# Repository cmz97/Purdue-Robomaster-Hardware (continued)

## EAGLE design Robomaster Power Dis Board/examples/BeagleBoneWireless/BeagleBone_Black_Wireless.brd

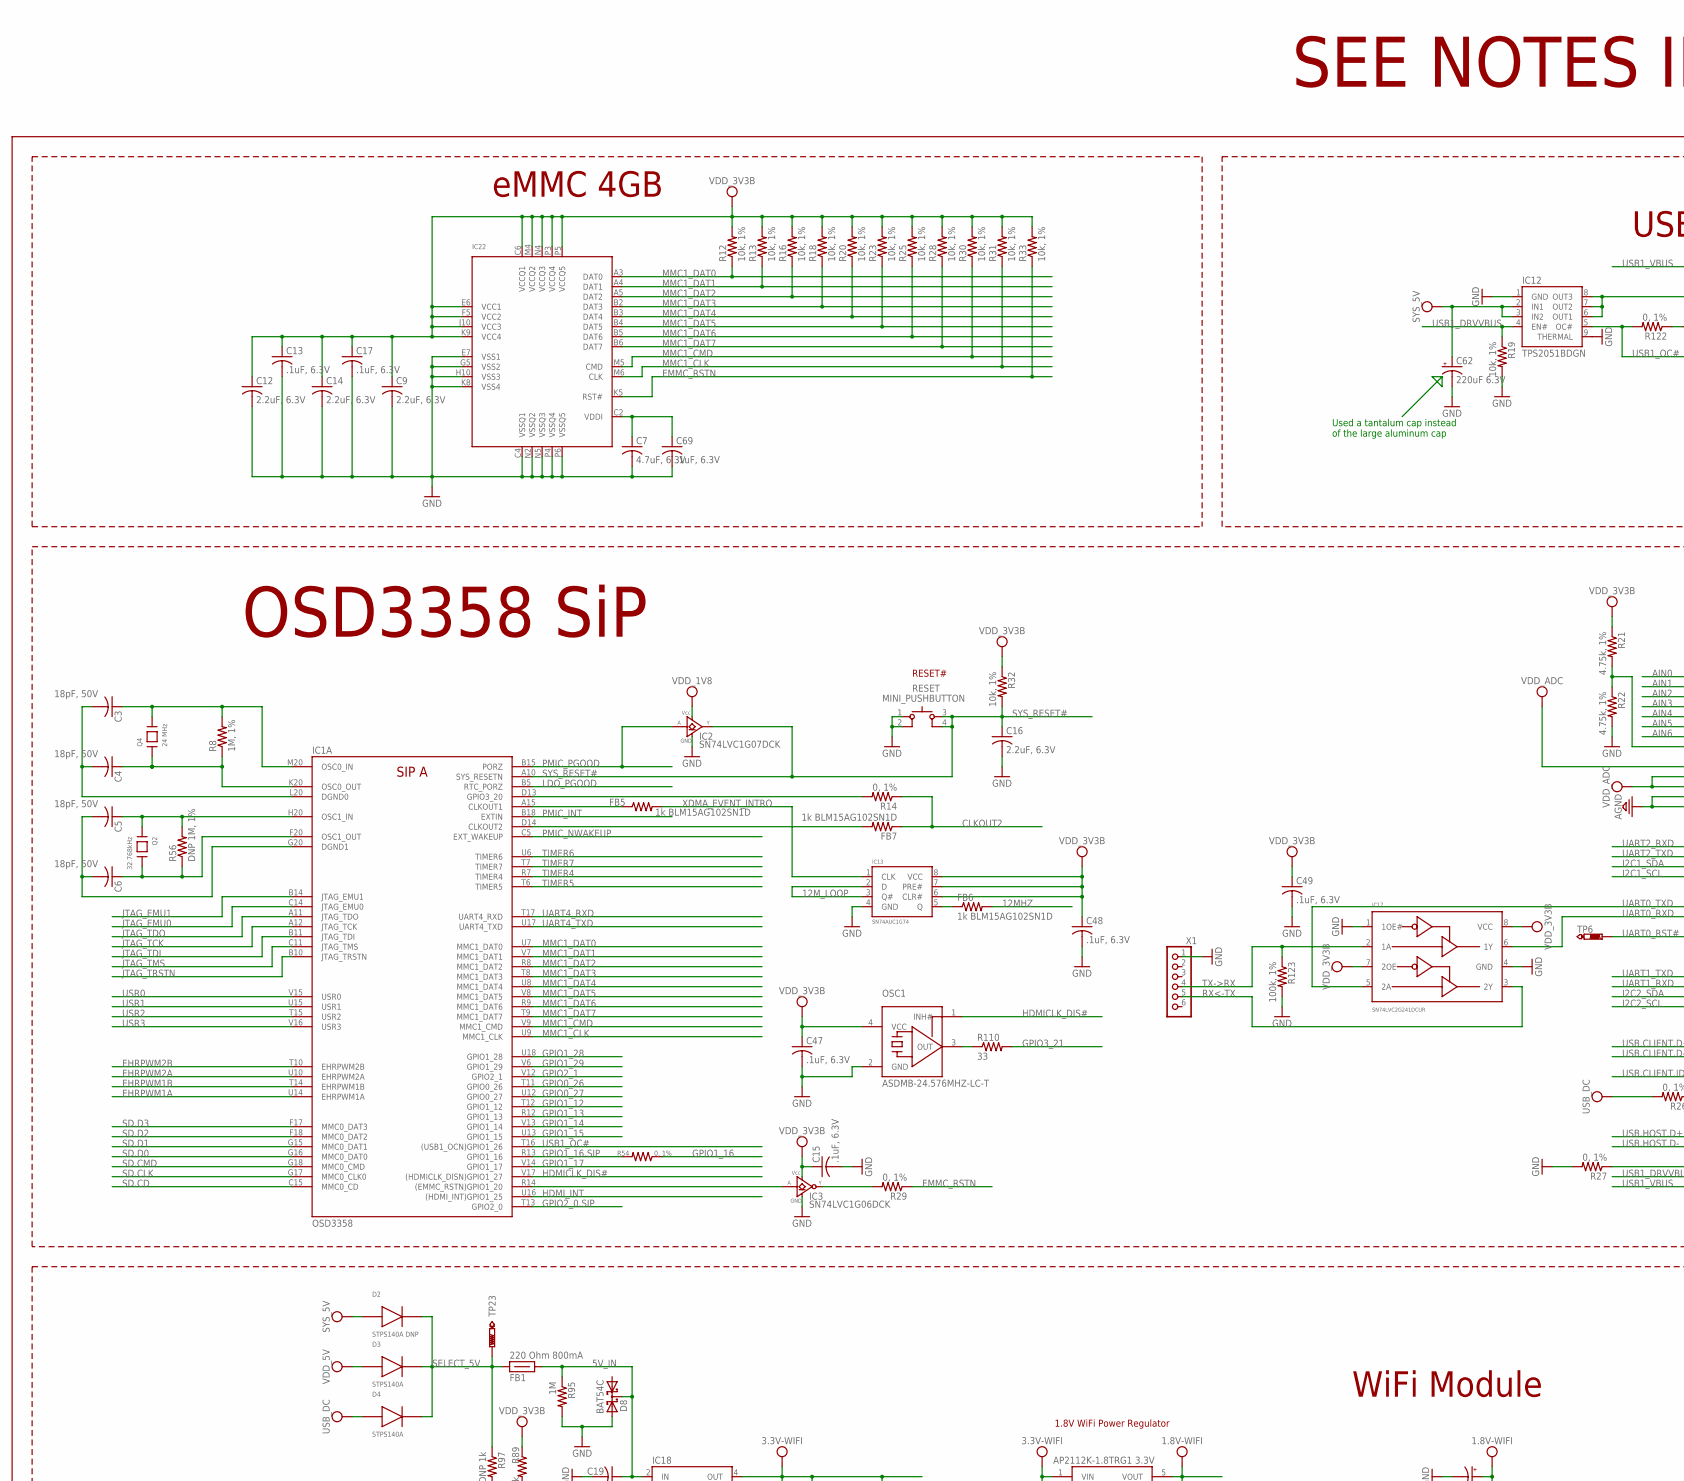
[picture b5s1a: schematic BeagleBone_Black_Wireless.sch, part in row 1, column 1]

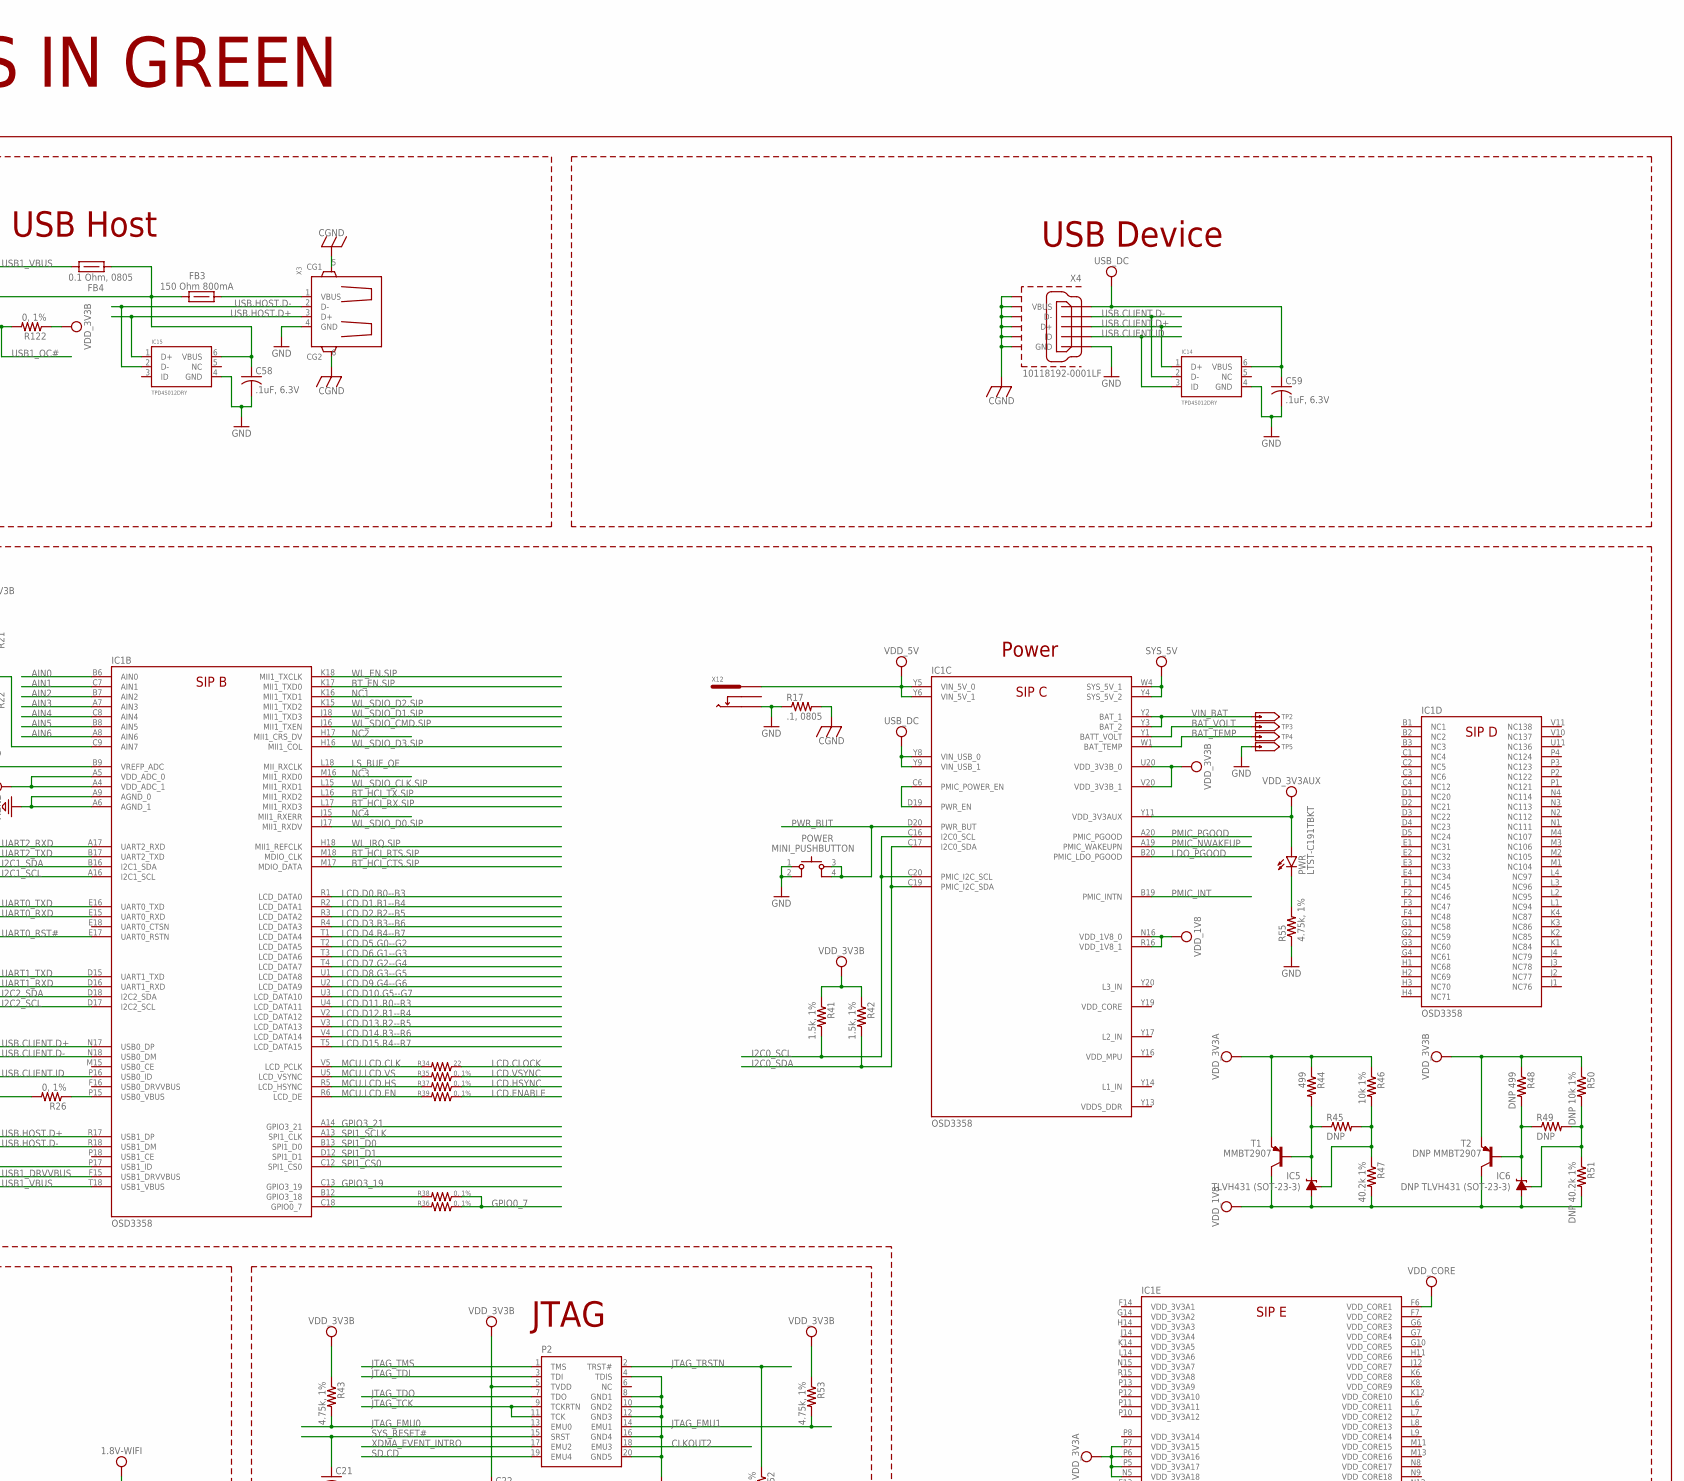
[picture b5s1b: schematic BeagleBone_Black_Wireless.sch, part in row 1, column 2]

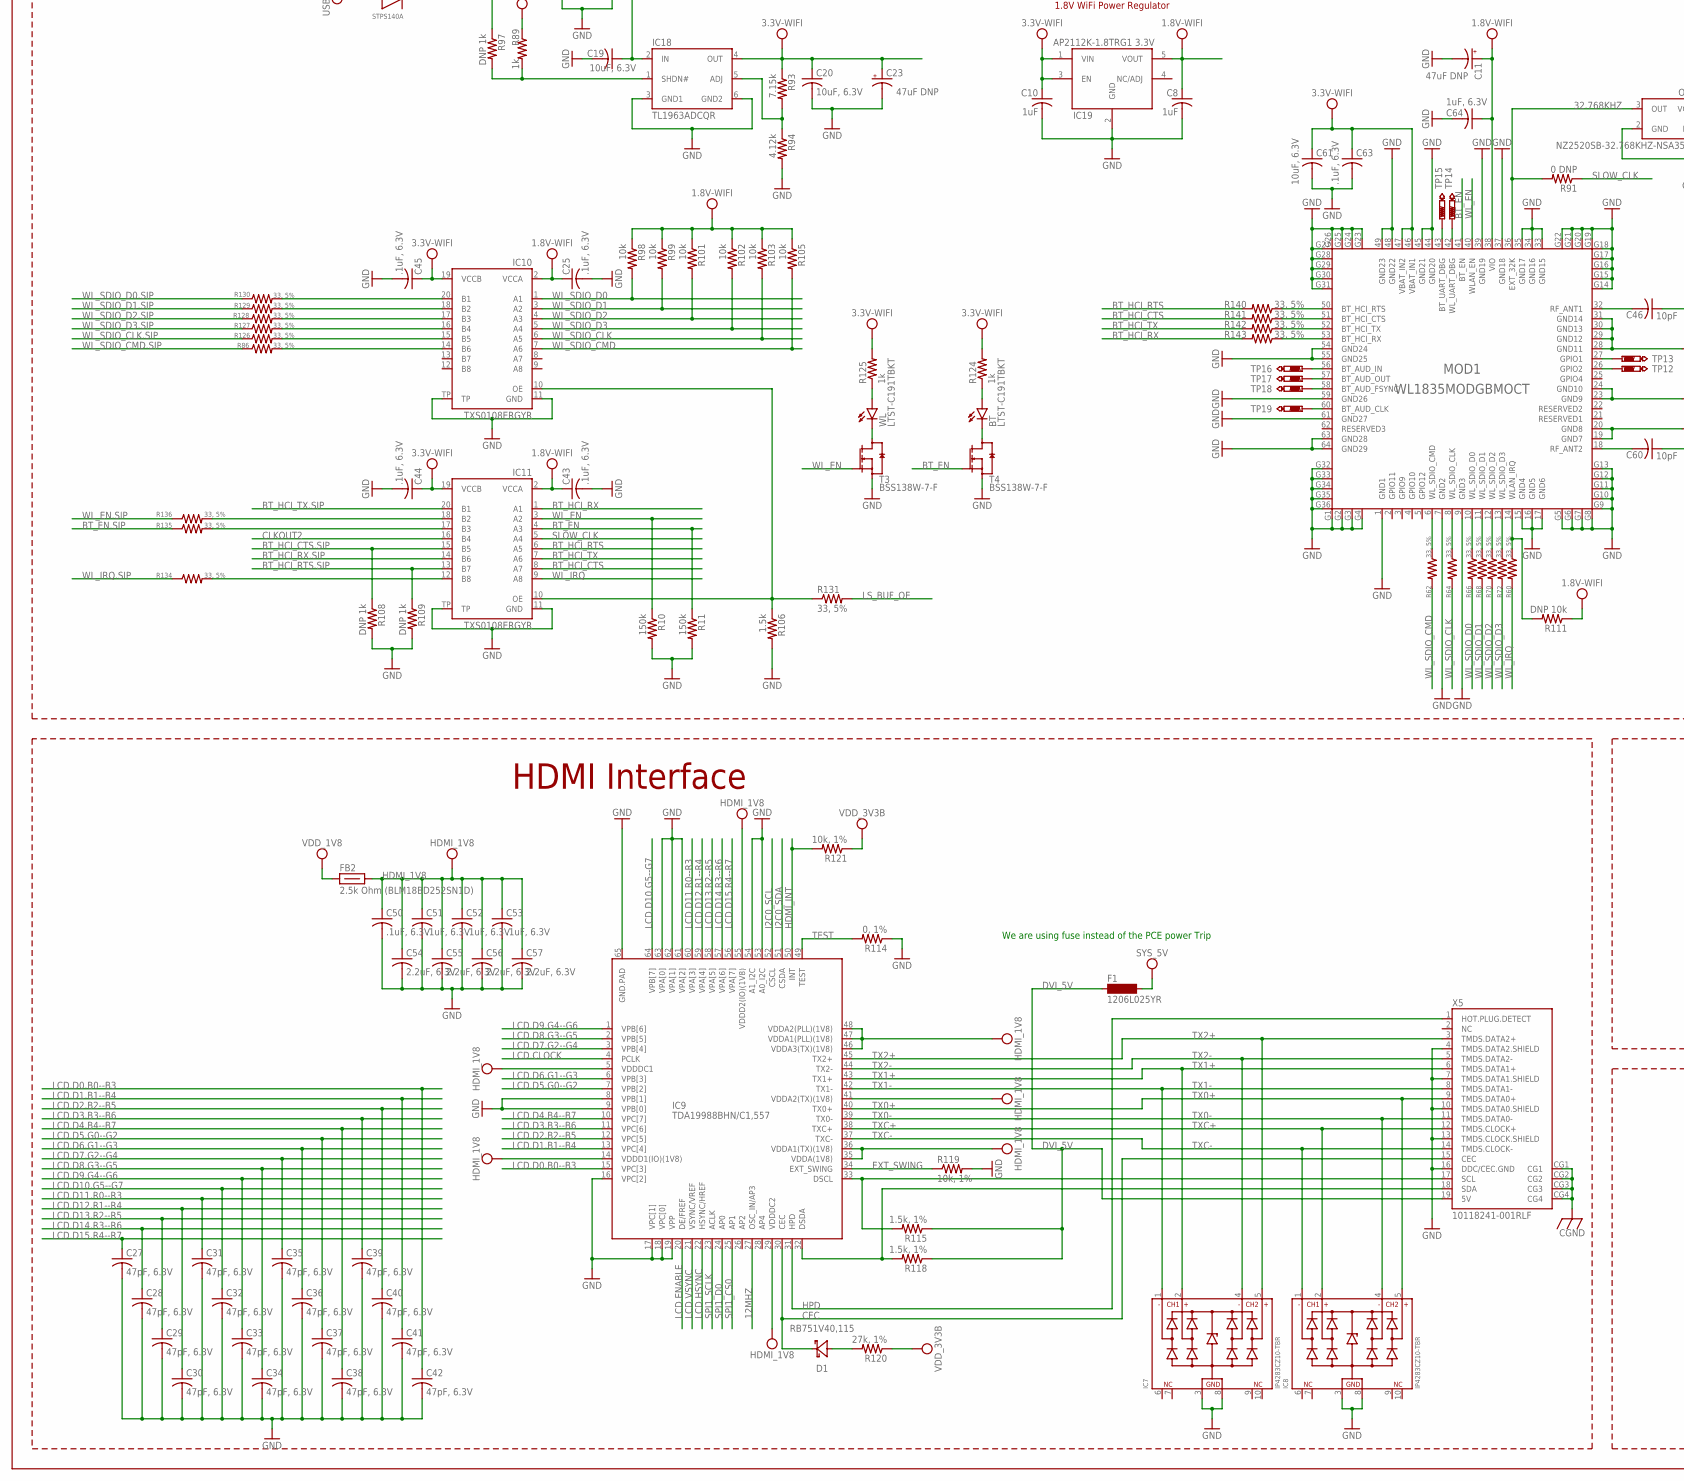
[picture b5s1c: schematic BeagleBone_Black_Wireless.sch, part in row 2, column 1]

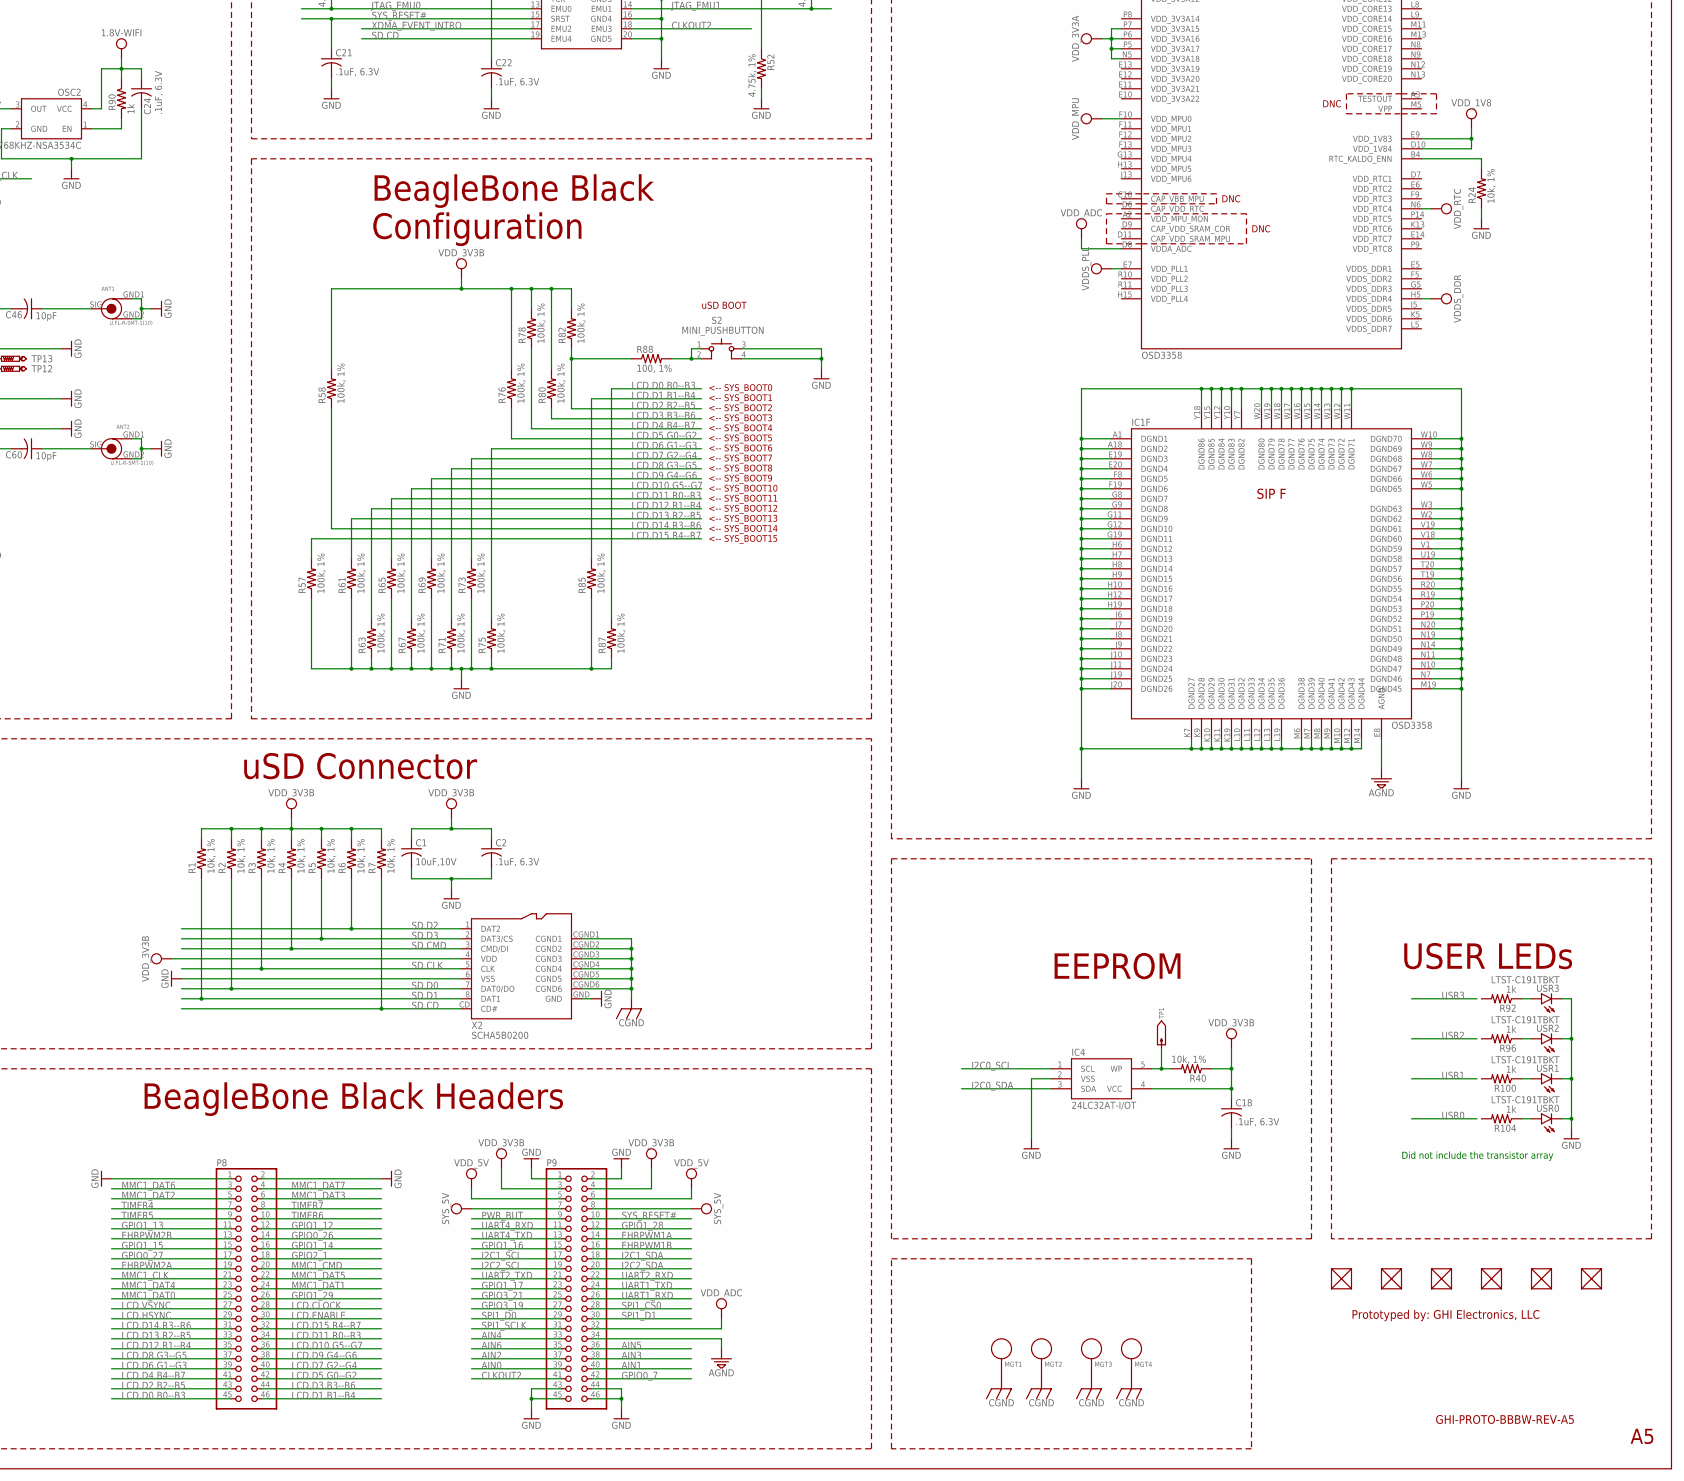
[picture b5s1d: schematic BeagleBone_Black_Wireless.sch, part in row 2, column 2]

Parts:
ANT1, ANT2: U.FL-R-SMT-1(10); U.FL-R-SMT-1
BT: LTST-C191TBKT; 0603-LED
C1: 10uF,10V; C0603K
C2, C13, C15, C17, C18, C21, C22, C24, C25, C43, C44, C45, C47, C48, C49, C50, C51, C52, C53, C58, C59, C63, C69: .1uF, 6.3V; C0402K
C3, C4, C5, C6: 18pF, 50V; C0402K
C7: 4.7uF, 6.3V; C0805K
C8, C10: 1uF; C0402K
C9, C12, C14: 2.2uF, 6.3V; C0805K
C11, C23: 47uF DNP; CT3528
C16, C54, C55, C56, C57: 2.2uF, 6.3V; C0603K
C19, C20, C61: 10uF, 6.3V; C0603K
C27, C28, C29, C30, C31, C32, C33, C34, C35, C36, C37, C38, C39, C40, C41, C42: 47pF, 6.3V; C0402K
C46, C60: 10pF; C0402K
C62: 220uF 6.3V; D/7343-31W
C64: 1uF, 6.3V; C0402K
D1: RB751V40,115; SOD323(NXP)REFLOW
D2: STPS140A DNP; DIODE_SMA
D3, D4: STPS140A; DIODE_SMA
D8: BAT54C; SOT23
F1: 1206L025YR; SM-1206
FB1: 220 Ohm 800mA; 0805-RESISTOR
FB2: 2.5k Ohm (BLM18BD252SN1D); 0805-RESISTOR
FB3: 150 Ohm 800mA; 0805-RESISTOR
FB4: 0.1 Ohm, 0805; 0805-RESISTOR
FB5, FB6, FB7: 1k BLM15AG102SN1D; R0402
FUD1, FUD2, FUD3, FUD4, FUD5, FUD6: FIDUCIAL; FIDUCIAL_40MIL
IC1: OSD3358
IC2: SN74LVC1G07DCK; SC70(TI-DCK)
IC3: SN74LVC1G06DCK; SC70(TI-DCK)
IC4: 24LC32AT-I/OT; SOT23-5(MICROCHIP)
IC5: TLVH431 (SOT-23-3); DBZ_R-PDSO-G3
IC6: DNP TLVH431 (SOT-23-3); DBZ_R-PDSO-G3
IC7, IC8: IP4283CZ10-TBR; SOT1176-1(NXP)
IC9: TDA19988BHN/C1,557; SOT804-4(NXP)
IC10, IC11: TXS0108ERGYR; R-PVQFN-N20(TI)
IC12: TPS2051BDGN; MSOP-POWER.PAD-8(TI)
IC13: SN74AUC1G74; SM8-8(TI)
IC14, IC15: TPD4S012DRY; SON-6(TI)-DRY
IC17: SN74LVC2G241DCUR; VSSOP8(TI)
IC18: TL1963ADCQR; SOT-223(DCQ_R-PDSO-G6_TI)
IC19: AP2112K-1.8TRG1 3.3V; SOT23-5
IC22: EMMC04G-S100-B08U; MICRON_EMMC_153
MGT1, MGT2, MGT3, MGT4: MOUNTING_HOLE
MOD1: WL1835MODGBMOCT; MOC-100(TI)
OSC1: ASDMB-24.576MHZ-LC-T; OSCILLATOR-2.5X2.0-BBB
OSC2: NZ2520SB-32.768KHZ-NSA3534C; NZ2520S
P2: JTAG
P8, P9: HEADER-2X23-(INCH)-0.1-TH; TH-2X23
POWER: MINI_PUSHBUTTON
PWR: LTST-C191TBKT; 0603-LED
Q2: 32.768kHz; CRYSTAL_3.2X1.5
Q4: 24 MHz; CRYSTAL_5X3.2MM
R1, R2, R3, R4, R5, R6, R7, R12, R13, R16, R18, R19, R20, R23, R24, R25, R28, R30, R31, R32, R33, R40, R119, R121: 10k, 1%; R0402
R8: 1M, 1%; R0402
R10, R11: 150k; R0402
R14, R26, R27, R29, R35, R36, R37, R38, R39, R54, R114, R122: 0, 1%; R0402
R17: .1, 0805; R0805
R21, R22, R43, R52, R53, R55: 4.75k, 1%; R0402
R34: 22; R0402
R41, R42, R115, R118: 1.5k, 1%; R0402
R44: 499; R0402
R45, R49: DNP; R0402
R46: 10k 1%; R0402
R47: 40.2k 1%; R0402
R48: DNP 499; R0402
R50: DNP 10k 1%; R0402
R51: DNP 40.2k 1%; R0402
R56: DNP 1M, 1%; R0402
R57, R58, R61, R63, R65, R67, R69, R71, R73, R75, R76, R78, R80, R82, R85, R87, R123: 100k, 1%; R0402
R60, R62, R64, R66, R68, R70, R72, R140, R141, R142, R143: 33, 5%; R0402
R86, R126, R127, R128, R129, R130, R131, R134, R135, R136: 33, 5%; R0603
R88: 100, 1%; R0402
R89, R90, R92, R96, R100, R104, R124, R125: 1k; R0402
R91: 0 DNP; R0402
R93: 7.15k; R0402
R94: 4.12k; R0402
R95: 1M; R0402
R97, R108, R109: DNP 1k; R0402
R98, R99, R101, R102, R103, R105: 10k; R0402
R106: 1.5k; R0402
R110: 33; R0402
R111: DNP 10k; R0402
R120: 27k, 1%; R0402
RESET: MINI_PUSHBUTTON
S2: MINI_PUSHBUTTON
T1: MMBT2907; SOT23-BEC
T2: DNP MMBT2907; SOT23-BEC
T3, T4: BSS138W-7-F; SOT-323(DIODES)
TP1, TP2, TP3, TP4, TP5: TESTPAD/W_HOLE_1X1
TP6, TP12, TP13, TP14, TP15, TP16, TP17, TP18, TP19, TP23: PTR1B1,27; B1,27
USR0, USR1, USR2, USR3: LTST-C191TBKT; 0603-LED
WL: LTST-C191TBKT; 0603-LED
X1: 1X6-(INCH)-0.1-TH; TH-1X6
X2: SCHA5B0200
X3: USB_HOST_W/CHASSIS_GND; USB_HOST_HORIZONTAL_W/CHASSIS_GND
X4: 10118192-0001LF; 10118192-0001LF(MICRO-USB-B-AMPHENOL-FCI)
X5: 10118241-001RLF; HDMI-TYPE-D-10118241
X12: PJ-102B_POWER_CON

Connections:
1.8V-WIFI: C8.1, C11.+, C24.1, C25.1, C43.1, C64.1, IC10.2 (VCCA), IC11.2 (VCCA), IC19.5 (VOUT), MOD1.38 (VIO), OSC2.4 (VCC), R90.1, R98.1, R99.1, R101.1, R102.1, R103.1, R105.1, R111.1
3.3V-WIFI: C10.1, C20.1, C23.+, C44.1, C45.1, C61.1, C63.1, IC10.19 (VCCB), IC11.19 (VCCB), IC18.4 (OUT), IC19.1 (VIN), IC19.3 (EN), MOD1.46 (VBAT_IN1), MOD1.47 (VBAT_IN2), R93.1, R124.2, R125.2
5V_IN: C19.1, D8.3 (CC), FB1.2, IC18.2 (IN), R95.1
12MHZ: FB6.2, IC9.27 (OSC_IN/AP3)
12M_LOOP: IC13.2 (D), IC13.3 (Q#)
32.768KHZ: MOD1.36 (EXT_32K), OSC2.3 (OUT), R91.2
AGND: IC1.A6 (AGND_1), IC1.A9 (AGND_0), IC1.E8 (AGND), P9.34
AIN0: IC1.B6 (AIN0), P9.39
AIN1: IC1.C7 (AIN1), P9.40
AIN2: IC1.B7 (AIN2), P9.37
AIN3: IC1.A7 (AIN3), P9.38
AIN4: IC1.C8 (AIN4), P9.33
AIN5: IC1.B8 (AIN5), P9.36
AIN6: IC1.A8 (AIN6), P9.35
AIN7: IC1.C9 (AIN7), R21.2, R22.1
ALT.BT.EN: IC11.17 (B3), R135.2
ALT.BUFF.OE: IC10.10 (OE), IC11.10 (OE), R106.1, R131.1
ALT.WL.CLK: IC10.15 (B5), R126.2
ALT.WL.CMD: IC10.14 (B6), R86.2
ALT.WL.D0: IC10.20 (B1), R130.2
ALT.WL.D1: IC10.18 (B2), R129.2
ALT.WL.D2: IC10.17 (B3), R128.2
ALT.WL.D3: IC10.16 (B4), R127.2
ALT.WL.EN: IC11.18 (B2), R136.2
ALT.WL.IRQ: IC11.12 (B8), R134.2
BAT_TEMP: IC1.W1 (BAT_TEMP), TP4.P$1
BAT_VOLT: IC1.Y1 (BATT_VOLT), TP3.P$1
BT_EN: IC11.4 (A3), MOD1.41 (BT_EN), R11.1, T4.G
BT_EN.SIP: IC1.K17 (MII1_TXD0), R135.1
BT_HCI_CTS: IC11.8 (A7), R141.2
BT_HCI_CTS.SIP: IC1.M17 (MDIO_DATA), IC11.15 (B5), R108.1
BT_HCI_RTS: IC11.6 (A5), R140.2
BT_HCI_RTS.SIP: IC1.M18 (MDIO_CLK), IC11.13 (B7), R109.1
BT_HCI_RX: IC11.1 (A1), R143.2
BT_HCI_RX.SIP: IC1.L17 (MII1_RXD3), IC11.14 (B6)
BT_HCI_TX: IC11.7 (A6), R142.2
BT_HCI_TX.SIP: IC1.L16 (MII1_RXD2), IC11.20 (B1)
CEC: D1.C (CATHODE), IC9.30 (CEC), X5.15 (CEC)
CGND: MGT1.P$1, MGT2.P$1, MGT3.P$1, MGT4.P$1, R17.2, X2.CGND1, X2.CGND2, X2.CGND3, X2.CGND4, X2.CGND5, X2.CGND6, X3.5 (CG1), X3.6 (CG2), X4.CGND1 (SGND1), X4.CGND2 (SGND2), X4.CGND3 (SGND3), X4.CGND4 (SGND4), X4.CGND5 (SGND5), X4.CGND6 (SGND6), X5.CG1, X5.CG2, X5.CG3, X5.CG4
CLKOUT2: FB7.1, IC11.16 (B4), P2.18 (EMU3), P9.41, R14.1
DVI_5V: F1.1, R115.1, R118.1, X5.19 (5V)
EHRPWM1A: IC1.U14 (EHRPWM1A), P9.14
EHRPWM1B: IC1.T14 (EHRPWM1B), P9.16
EHRPWM2A: IC1.U10 (EHRPWM2A), P8.19
EHRPWM2B: IC1.T10 (EHRPWM2B), P8.13
EMMC_RSTN: IC22.K5 (RST#), R29.1, R33.1
EXT_SWING: IC9.34 (EXT_SWING), R119.1
GND: ANT1.GND1, ANT1.GND2, ANT2.GND1, ANT2.GND2, C1.2, C2.2, C7.2, C8.2, C9.2, C10.2, C11.-, C12.2, C13.2, C14.2, C15.2, C16.2, C17.2, C18.2, C19.2, C20.2, C21.2, C22.2, C23.-, C24.2, C25.2, C27.2, C28.2, C29.2, C30.2, C31.2, C32.2, C33.2, C34.2, C35.2, C36.2, C37.2, C38.2, C39.2, C40.2, C41.2, C42.2, C43.2, C44.2, C45.2, C47.2, C48.2, C49.2, C50.2, C51.2, C52.2, C53.2, C54.2, C55.2, C56.2, C57.2, C58.2, C59.2, C61.2, C62.-, C63.2, C64.2, C69.2, D8.2 (A2), IC1.A1 (DGND1), IC1.A18 (DGND2), IC1.E19 (DGND3), IC1.E20 (DGND4), IC1.F8 (DGND5), IC1.F19 (DGND6), IC1.G8 (DGND7), IC1.G9 (DGND8), IC1.G11 (DGND9), IC1.G12 (DGND10), IC1.G19 (DGND11), IC1.H6 (DGND12), IC1.H7 (DGND13), IC1.H8 (DGND14), IC1.H9 (DGND15), IC1.H10 (DGND16), IC1.H12 (DGND17), IC1.H19 (DGND18), IC1.J6 (DGND19), IC1.J7 (DGND20), IC1.J8 (DGND21), IC1.J9 (DGND22), IC1.J10 (DGND23), IC1.J11 (DGND24), IC1.J19 (DGND25), IC1.J20 (DGND26), IC1.K7 (DGND27), IC1.K9 (DGND28), IC1.K10 (DGND29), IC1.K11 (DGND30), IC1.K19 (DGND31), IC1.L10 (DGND32), IC1.L11 (DGND33), IC1.L12 (DGND34), IC1.L13 (DGND35), IC1.L19 (DGND36), IC1.M6 (DGND38), IC1.M7 (DGND39), IC1.M8 (DGND40), IC1.M9 (DGND41), IC1.M10 (DGND42), IC1.M12 (DGND43), IC1.M14 (DGND44), IC1.M19 (DGND45), IC1.N7 (DGND46), IC1.N10 (DGND47), IC1.N11 (DGND48), IC1.N14 (DGND49), IC1.N19 (DGND50), IC1.N20 (DGND51), IC1.P19 (DGND52), IC1.P20 (DGND53), IC1.R19 (DGND54), IC1.R20 (DGND55), IC1.T19 (DGND56), IC1.T20 (DGND57), IC1.U19 (DGND58), IC1.V1 (DGND59), IC1.V18 (DGND60), IC1.V19 (DGND61), IC1.W2 (DGND62), IC1.W3 (DGND63), IC1.W5 (DGND65), IC1.W6 (DGND66), IC1.W7 (DGND67), IC1.W8 (DGND68), IC1.W9 (DGND69), IC1.W10 (DGND70), IC1.W11 (DGND71), IC1.W12 (DGND72), IC1.W13 (DGND73), IC1.W14 (DGND74), IC1.W15 (DGND75), IC1.W16 (DGND76), IC1.W17 (DGND77), IC1.W18 (DGND78), IC1.W19 (DGND79), IC1.W20 (DGND80), IC1.Y7 (DGND82), IC1.Y10 (DGND83), IC1.Y12 (DGND84), IC1.Y15 (DGND85), IC1.Y18 (DGND86), IC2.3 (GND), IC3.3 (GND), IC4.2 (VSS), IC7.3 (GND1), IC7.8 (GND2), IC8.3 (GND1), IC8.8 (GND2), IC9.8 (VPB[1]), IC9.9 (VPB[0]), IC9.16 (VPC[2]), IC9.17 (VPC[1]), IC9.18 (VPC[0]), IC9.19 (VPP), IC9.53 (A0_I2C), IC9.54 (A1_I2C), IC9.61 (VPA[2]), IC9.62 (VPA[1]), IC9.63 (VPA[0]), IC9.65 (GND.PAD), IC10.11 (GND), IC10.TP, IC11.11 (GND), IC11.TP, IC12.1 (GND), IC12.9 (THERMAL), IC13.4 (GND), IC14.4 (GND), IC15.4 (GND), IC17.1 (1OE#), IC17.4 (GND), IC18.3 (GND1), IC18.6 (GND2), IC19.2 (GND), IC22.C4 (VSSQ1), IC22.E7 (VSS1), IC22.G5 (VSS2), IC22.H10 (VSS3), IC22.K8 (VSS4), IC22.N2 (VSSQ2), IC22.N5 (VSSQ3), IC22.P4 (VSSQ4), IC22.P6 (VSSQ5), MOD1.1 (GND1), MOD1.7 (GND2), MOD1.9 (GND3), MOD1.15 (GND4), MOD1.16 (GND5), MOD1.17 (GND6), MOD1.19 (GND7), MOD1.20 (GND8), MOD1.23 (GND9), MOD1.24 (GND10), MOD1.28 (GND11), MOD1.29 (GND12), MOD1.30 (GND13), MOD1.31 (GND14), MOD1.33 (GND15), MOD1.34 (GND16), MOD1.35 (GND17), MOD1.37 (GND18), MOD1.39 (GND19), MOD1.44 (GND20), MOD1.45 (GND21), MOD1.48 (GND22), MOD1.49 (GND23), MOD1.54 (GND24), MOD1.55 (GND25), MOD1.59 (GND26), MOD1.61 (GND27), MOD1.63 (GND28), MOD1.64 (GND29), MOD1.G1, MOD1.G2, MOD1.G3, MOD1.G4, MOD1.G5, MOD1.G6, MOD1.G7, MOD1.G8, MOD1.G9, MOD1.G10, MOD1.G11, MOD1.G12, MOD1.G13, MOD1.G14, MOD1.G15, MOD1.G16, MOD1.G17, MOD1.G18, MOD1.G19, MOD1.G20, MOD1.G21, MOD1.G22, MOD1.G23, MOD1.G24, MOD1.G25, MOD1.G26, MOD1.G27, MOD1.G28, MOD1.G29, MOD1.G30, MOD1.G31, MOD1.G32, MOD1.G33, MOD1.G34, MOD1.G35, MOD1.G36, OSC1.2 (GND), OSC2.2 (GND), P2.4 (TDIS), P2.8 (GND1), P2.10 (GND2), P2.12 (GND3), P2.16 (GND4), P2.20 (GND5), P8.1, P8.2, P9.1, P9.2, P9.43, P9.44, P9.45, P9.46, POWER.1, POWER.2, R10.2, R11.2, R17.1, R19.2, R22.2, R24.1, R27.2, R52.2, R55.1, R57.1, R61.1, R63.1, R65.1, R67.1, R69.1, R71.1, R73.1, R75.1, R85.1, R87.1, R94.2, R95.2, R106.2, R108.2, R109.2, R114.1, R119.2, R123.2, RESET.1, RESET.2, S2.3, S2.4, T3.S, T4.S, TP5.P$1, USR0.K, USR1.K, USR2.K, USR3.K, X1.1, X2.6 (VSS), X2.GND, X3.4 (GND), X4.GND, X5.4 (TMDS.DATA2.SHIELD), X5.7 (TMDS.DATA1.SHIELD), X5.10 (TMDS.DATA0.SHIELD), X5.13 (TMDS.CLOCK.SHIELD), X5.16 (DDC/CEC.GND), X12.OUT
GPIO0_7: P9.42, R36.1, R38.1
GPIO0_26: IC1.T11 (GPIO0_26), P8.14
GPIO0_27: IC1.U12 (GPIO0_27), P8.17
GPIO1_12: IC1.T12 (GPIO1_12), P8.12
GPIO1_13: IC1.R12 (GPIO1_13), P8.11
GPIO1_14: IC1.V13 (GPIO1_14), P8.16
GPIO1_15: IC1.U13 (GPIO1_15), P8.15
GPIO1_16: P9.15, R54.1
GPIO1_16.SIP: IC1.R13 (GPIO1_16), R54.2
GPIO1_17: IC1.V14 (GPIO1_17), P9.23
GPIO1_28: IC1.U18 (GPIO1_28), P9.12
GPIO1_29: IC1.V6 (GPIO1_29), P8.26
GPIO2_0.SIP: IC1.T13 (GPIO2_0)
GPIO2_1: IC1.V12 (GPIO2_1), P8.18
GPIO3_19: IC1.C13 (GPIO3_19), P9.27
GPIO3_21: IC1.A14 (GPIO3_21), P9.25, R110.2
HDMI.DSCL: IC9.33 (DSCL), R115.2, X5.17 (SCL)
HDMI.DSDA: IC9.32 (DSDA), R118.2, X5.18 (SDA)
HDMICLK_DIS#: IC1.V17 ((HDMICLK_DISN)GPIO1_27), OSC1.1 (INH#)
HDMI_1V8: C50.1, C51.1, C52.1, C53.1, C54.1, C55.1, C56.1, C57.1, FB2.2, IC9.5 (VDDDC1), IC9.14 (VDDD1(IO)(1V8)), IC9.29 (VDDDC2), IC9.35 (VDDA(1V8)), IC9.36 (VDDA1(TX)(1V8)), IC9.41 (VDDA2(TX)(1V8)), IC9.46 (VDDA3(TX)(1V8)), IC9.47 (VDDA1(PLL)(1V8)), IC9.48 (VDDA2(PLL)(1V8)), IC9.55 (VDDD2(IO)(1V8))
HDMI_INT: IC1.U16 ((HDMI_INT)GPIO1_25), IC9.50 (INT), R121.2
HPD: IC9.31 (HPD), X5.1 (HOT.PLUG.DETECT)
I2C0_SCL: IC1.C16 (I2C0_SCL), IC1.C20 (PMIC_I2C_SCL), IC4.1 (SCL), IC9.52 (CSCL), R41.2
I2C0_SDA: IC1.C17 (I2C0_SDA), IC1.C19 (PMIC_I2C_SDA), IC4.3 (SDA), IC9.51 (CSDA), R42.2
I2C1_SCL: IC1.A16 (I2C1_SCL), P9.17
I2C1_SDA: IC1.B16 (I2C1_SDA), P9.18
I2C2_SCL: IC1.D17 (I2C2_SCL), P9.19
I2C2_SDA: IC1.D18 (I2C2_SDA), P9.20
JTAG_EMU0: IC1.C14 (JTAG_EMU0), P2.13 (EMU0), R43.2
JTAG_EMU1: IC1.B14 (JTAG_EMU1), P2.14 (EMU1), R53.2
JTAG_TCK: IC1.A12 (JTAG_TCK), P2.9 (TCKRTN), P2.11 (TCK)
JTAG_TDI: IC1.B11 (JTAG_TDI), P2.3 (TDI)
JTAG_TDO: IC1.A11 (JTAG_TDO), P2.7 (TDO)
JTAG_TMS: IC1.C11 (JTAG_TMS), P2.1 (TMS)
JTAG_TRSTN: IC1.B10 (JTAG_TRSTN), P2.2 (TRST#), R52.1
LCD.CLOCK: IC9.4 (PCLK), P8.28, R34.1
LCD.D0.B0--B3: C42.1, IC1.R1 (LCD_DATA0), IC9.15 (VPC[3]), P8.45, R87.2
LCD.D1.B1--B4: C41.1, IC1.R2 (LCD_DATA1), IC9.13 (VPC[4]), P8.46, R85.2
LCD.D2.B2--B5: C40.1, IC1.R3 (LCD_DATA2), IC9.12 (VPC[5]), P8.43, R82.1, R88.1
LCD.D3.B3--B6: C39.1, IC1.R4 (LCD_DATA3), IC9.11 (VPC[6]), P8.44, R80.1
LCD.D4.B4--B7: C38.1, IC1.T1 (LCD_DATA4), IC9.10 (VPC[7]), P8.41, R78.1
LCD.D5.G0--G2: C37.1, IC1.T2 (LCD_DATA5), IC9.7 (VPB[2]), P8.42, R76.1
LCD.D6.G1--G3: C36.1, IC1.T3 (LCD_DATA6), IC9.6 (VPB[3]), P8.39, R75.2
LCD.D7.G2--G4: C35.1, IC1.T4 (LCD_DATA7), IC9.3 (VPB[4]), P8.40, R73.2
LCD.D8.G3--G5: C34.1, IC1.U1 (LCD_DATA8), IC9.2 (VPB[5]), P8.37, R71.2
LCD.D9.G4--G6: C33.1, IC1.U2 (LCD_DATA9), IC9.1 (VPB[6]), P8.38, R69.2
LCD.D10.G5--G7: C32.1, IC1.U3 (LCD_DATA10), IC9.64 (VPB[7]), P8.36, R67.2
LCD.D11.R0--R3: C31.1, IC1.U4 (LCD_DATA11), IC9.60 (VPA[3]), P8.34, R65.2
LCD.D12.R1--R4: C30.1, IC1.V2 (LCD_DATA12), IC9.59 (VPA[4]), P8.35, R63.2
LCD.D13.R2--R5: C29.1, IC1.V3 (LCD_DATA13), IC9.58 (VPA[5]), P8.33, R61.2
LCD.D14.R3--R6: C28.1, IC1.V4 (LCD_DATA14), IC9.57 (VPA[6]), P8.31, R58.1
LCD.D15.R4--R7: C27.1, IC1.T5 (LCD_DATA15), IC9.56 (VPA[7]), P8.32, R57.2
LCD.ENABLE: IC9.20 (DE/FREF), P8.30, R39.1
LCD.HSYNC: IC9.22 (HSYNC/HREF), P8.29, R37.1
LCD.VSYNC: IC9.21 (VSYNC/VREF), P8.27, R35.1
LDO_PGOOD: IC1.B5 (RTC_PORZ), IC1.B20 (PMIC_LDO_PGOOD)
LS_BUF_OE: IC1.L18 (MII_RXCLK), R131.2
MCU.LCD.CLK: IC1.V5 (LCD_PCLK), R34.2
MCU.LCD.EN: IC1.R6 (LCD_DE), R39.2
MCU.LCD.HS: IC1.R5 (LCD_HSYNC), R37.2
MCU.LCD.VS: IC1.U5 (LCD_VSYNC), R35.2
MMC1_CLK: IC1.U9 (MMC1_CLK), IC22.M6 (CLK), P8.21, R31.1
MMC1_CMD: IC1.V9 (MMC1_CMD), IC22.M5 (CMD), P8.20, R30.1
MMC1_DAT0: IC1.U7 (MMC1_DAT0), IC22.A3 (DAT0), P8.25, R12.1
MMC1_DAT1: IC1.V7 (MMC1_DAT1), IC22.A4 (DAT1), P8.24, R13.1
MMC1_DAT2: IC1.R8 (MMC1_DAT2), IC22.A5 (DAT2), P8.5, R16.1
MMC1_DAT3: IC1.T8 (MMC1_DAT3), IC22.B2 (DAT3), P8.6, R18.1
MMC1_DAT4: IC1.U8 (MMC1_DAT4), IC22.B3 (DAT4), P8.23, R20.1
MMC1_DAT5: IC1.V8 (MMC1_DAT5), IC22.B4 (DAT5), P8.22, R23.1
MMC1_DAT6: IC1.R9 (MMC1_DAT6), IC22.B5 (DAT6), P8.3, R25.1
MMC1_DAT7: IC1.T9 (MMC1_DAT7), IC22.B6 (DAT7), P8.4, R28.1
unnamed: OSC2.1 (EN), R90.2
unnamed: R88.2, S2.1, S2.2
unnamed: FB5.1, IC1.A15 (CLKOUT1)
unnamed: PWR.K, R55.2
unnamed: IC18.1 (SHDN#), R89.2, R97.2
unnamed: C4.1, IC1.K20 (OSC0_OUT), Q4.1, R8.1
unnamed: C3.1, IC1.M20 (OSC0_IN), Q4.2, R8.2
unnamed: IC1.C6 (PMIC_POWER_EN), IC1.D19 (PWR_EN)
unnamed: IC18.5 (ADJ), R93.2, R94.1
unnamed: C3.2, C4.2, IC1.L20 (DGND0)
unnamed: C5.2, C6.2, IC1.G20 (DGND1)
unnamed: ANT2.SIG, C60.1
unnamed: ANT1.SIG, C46.1
unnamed: C46.2, MOD1.32 (RF_ANT1)
unnamed: R100.1, USR1.A
unnamed: R96.1, USR2.A
unnamed: R92.1, USR3.A
unnamed: C60.2, MOD1.18 (RF_ANT2)
unnamed: IC1.P17 (USB1_ID), R27.1
unnamed: IC1.B4 (RTC_KALDO_ENN), R24.2
unnamed: T3.D, WL.K
unnamed: IC1.D13 (GPIO3_20), R14.2
unnamed: FB7.2, IC1.D14 (CLKOUT2)
unnamed: IC1.R14 ((EMMC_RSTN)GPIO1_20), IC3.2 (A)
unnamed: IC3.4 (Y), R29.2
unnamed: MOD1.26 (GPIO2), TP12.TP
unnamed: R104.1, USR0.A
unnamed: MOD1.27 (GPIO1), TP13.TP
unnamed: C5.1, IC1.H20 (OSC1_IN), Q2.P$1, R56.2
unnamed: C6.1, IC1.F20 (OSC1_OUT), Q2.P$2, R56.1
unnamed: MOD1.42 (WL_UART_DBG), TP14.TP
unnamed: MOD1.43 (BT_UART_DBG), TP15.TP
unnamed: MOD1.56 (BT_AUD_IN), TP16.TP
unnamed: MOD1.57 (BT_AUD_OUT), TP17.TP
unnamed: OSC1.3 (OUT), R110.1
unnamed: MOD1.58 (BT_AUD_FSYNC), TP18.TP
unnamed: MOD1.60 (BT_AUD_CLK), TP19.TP
unnamed: IC1.P15 (USB0_VBUS), R26.1
unnamed: C7.1, C69.1, IC22.C2 (VDDI)
unnamed: IC1.C18 (GPIO0_7), R36.2
unnamed: IC1.B12 (GPIO3_18), R38.2
unnamed: IC5.2 (C), R44.2, R45.1, T1.B
unnamed: IC5.1 (FB), R45.2, R46.2, R47.1
unnamed: IC6.2 (C), R48.2, R49.1, T2.B
unnamed: IC6.1 (FB), R49.2, R50.2, R51.1
unnamed: IC4.5 (WP), R40.2, TP1.P$1
unnamed: BT.K, T4.D
unnamed: R125.1, WL.A
unnamed: FB6.1, IC13.5 (Q)
unnamed: BT.A, R124.1
unnamed: MOD1.14 (WLAN_IRQ), R60.1, R111.2
unnamed: MOD1.13 (WL_SDIO_D3), R72.1
unnamed: MOD1.12 (WL_SDIO_D2), R70.1
unnamed: MOD1.11 (WL_SDIO_D1), R68.1
unnamed: D1.A (ANODE), R120.2
unnamed: MOD1.10 (WL_SDIO_D0), R66.1
unnamed: MOD1.8 (WL_SDIO_CLK), R64.1
unnamed: MOD1.6 (WL_SDIO_CMD), R62.1
unnamed: MOD1.50 (BT_HCI_RTS), R140.1
unnamed: MOD1.51 (BT_HCI_CTS), R141.1
unnamed: MOD1.52 (BT_HCI_TX), R142.1
unnamed: MOD1.53 (BT_HCI_RX), R143.1
NC1: IC1.K16 (MII1_TXD1)
NC2: IC1.H17 (MII1_CRS_DV)
NC3: IC1.M16 (MII1_RXD0)
NC4: IC1.J15 (MII1_RXERR)
PMIC_INT: IC1.B18 (EXTIN), IC1.B19 (PMIC_INTN)
PMIC_NWAKEUP: IC1.A19 (PMIC_WAKEUPN), IC1.C5 (EXT_WAKEUP)
PMIC_PGOOD: IC1.A20 (PMIC_PGOOD), IC1.B15 (PORZ), IC2.2 (A)
PWR_BUT: IC1.D20 (PWR_BUT), P9.9, POWER.3, POWER.4
RX<-TX: IC17.3 (2Y), X1.5
SD.CD: IC1.C15 (MMC0_CD), P2.19 (EMU4), R7.1, X2.CD (CD#)
SD.CLK: IC1.G17 (MMC0_CLK0), R3.1, X2.5 (CLK)
SD.CMD: IC1.G18 (MMC0_CMD), R4.1, X2.3 (CMD/DI)
SD.D0: IC1.G16 (MMC0_DAT0), R2.1, X2.7 (DAT0/DO)
SD.D1: IC1.G15 (MMC0_DAT1), R1.1, X2.8 (DAT1)
SD.D2: IC1.F18 (MMC0_DAT2), R6.1, X2.1 (DAT2)
SD.D3: IC1.F17 (MMC0_DAT3), R5.1, X2.2 (DAT3/CS)
SELECT_5V: D2.K, D3.K, D4.K, FB1.1, R97.1, TP23.TP
SLOW_CLK: IC11.5 (A4), R91.1
SPI1_CS0: IC1.C12 (SPI1_CS0), IC9.25 (AP1), P9.28
SPI1_D0: IC1.B13 (SPI1_D0), IC9.24 (AP0), P9.29
SPI1_D1: IC1.D12 (SPI1_D1), P9.30
SPI1_SCLK: IC1.A13 (SPI1_CLK), IC9.23 (ACLK), P9.31
SYS_5V: C62.+, D2.A, F1.2, IC1.W4 (SYS_5V_1), IC1.Y4 (SYS_5V_2), IC12.2 (IN1), IC12.3 (IN2), P9.7, P9.8
SYS_RESET#: C16.1, C21.1, IC1.A10 (SYS_RESETN), IC2.4 (Y), P2.15 (SRST), P9.10, R32.2, RESET.3, RESET.4
TEST: IC9.49 (TEST), R114.2
TIMER4: IC1.R7 (TIMER4), P8.7
TIMER5: IC1.T6 (TIMER5), P8.9
TIMER6: IC1.U6 (TIMER6), P8.10
TIMER7: IC1.T7 (TIMER7), P8.8
TX0+: IC8.5 (TMDS.CH2+), IC9.40 (TX0+), X5.9 (TMDS.DATA0+)
TX0-: IC8.4 (TMDS.CH2-), IC9.39 (TX0-), X5.11 (TMDS.DATA0-)
TX1+: IC7.2 (TMDS.CH1+), IC9.43 (TX1+), X5.6 (TMDS.DATA1+)
TX1-: IC7.1 (TMDS.CH1-), IC9.42 (TX1-), X5.8 (TMDS.DATA1-)
TX2+: IC7.5 (TMDS.CH2+), IC9.45 (TX2+), X5.3 (TMDS.DATA2+)
TX2-: IC7.4 (TMDS.CH2-), IC9.44 (TX2-), X5.5 (TMDS.DATA2-)
TX->RX: IC17.2 (1A), R123.1, X1.4
TXC+: IC8.2 (TMDS.CH1+), IC9.38 (TXC+), X5.12 (TMDS.CLOCK+)
TXC-: IC8.1 (TMDS.CH1-), IC9.37 (TXC-), X5.14 (TMDS.CLOCK-)
UART0_RST#: IC1.E17 (UART0_RSTN), TP6.TP
UART0_RXD: IC1.E15 (UART0_RXD), IC17.6 (1Y)
UART0_TXD: IC1.E16 (UART0_TXD), IC17.5 (2A)
UART1_RXD: IC1.D16 (UART1_RXD), P9.26
UART1_TXD: IC1.D15 (UART1_TXD), P9.24
UART2_RXD: IC1.A17 (UART2_RXD), P9.22
UART2_TXD: IC1.B17 (UART2_TXD), P9.21
UART4_RXD: IC1.T17 (UART4_RXD), P9.11
UART4_TXD: IC1.U17 (UART4_TXD), P9.13
USB1_DRVVBUS: IC1.F15 (USB1_DRVVBUS), IC12.4 (EN#), R19.1
USB1_OC#: IC1.T16 ((USB1_OCN)GPIO1_26), IC12.5 (OC#), R122.2
USB1_VBUS: FB4.2, IC1.T18 (USB1_VBUS)
USB.CLIENT.D+: IC1.N17 (USB0_DP), IC14.1 (D+), X4.D+
USB.CLIENT.D-: IC1.N18 (USB0_DM), IC14.2 (D-), X4.D-
USB.CLIENT.ID: IC1.P16 (USB0_ID), IC14.3 (ID), X4.ID
USB.HOST.D+: IC1.R17 (USB1_DP), IC15.1 (D+), X3.3 (D+)
USB.HOST.D-: IC1.R18 (USB1_DM), IC15.2 (D-), X3.2 (D-)
USB_DC: C59.1, D4.A, IC1.Y8 (VIN_USB_0), IC1.Y9 (VIN_USB_1), IC14.6 (VBUS), R26.2, X4.VBUS
USR0: IC1.V15 (USR0), R104.2
USR1: IC1.U15 (USR1), R100.2
USR2: IC1.T15 (USR2), R96.2
USR3: IC1.V16 (USR3), R92.2
VBUS.HOST: FB3.2, X3.1 (VBUS)
VBUS.OUT: C58.1, FB3.1, FB4.1, IC12.6 (OUT1), IC12.7 (OUT2), IC12.8 (OUT3), IC15.6 (VBUS)
VDDS_DDR: IC1.H5 (VDDS_DDR4)
VDDS_PLL: IC1.E7 (VDD_PLL1)
VDD_1V8: FB2.1, IC1.D10 (VDD_1V84), IC1.E9 (VDD_1V83), IC1.N16 (VDD_1V8_0), IC1.R16 (VDD_1V8_1), IC2.5 (VCC), IC5.3 (A), IC6.3 (A), R47.2, R51.2, T1.C, T2.C
VDD_3V3A: IC1.N5 (VDD_3V3A18), IC1.P5 (VDD_3V3A17), IC1.P6 (VDD_3V3A16), IC1.P7 (VDD_3V3A15), R44.1, R46.1, T1.E
VDD_3V3AUX: IC1.Y11 (VDD_3V3AUX), PWR.A
VDD_3V3B: C1.1, C2.1, C9.1, C12.1, C13.1, C14.1, C15.1, C17.1, C18.1, C22.1, C47.1, C48.1, C49.1, IC1.U20 (VDD_3V3B_0), IC1.V20 (VDD_3V3B_1), IC3.5 (VCC), IC4.4 (VCC), IC13.6 (CLR#), IC13.7 (PRE#), IC13.8 (VCC), IC17.7 (2OE), IC17.8 (VCC), IC22.C6 (VCCQ1), IC22.E6 (VCC1), IC22.F5 (VCC2), IC22.J10 (VCC3), IC22.K9 (VCC4), IC22.M4 (VCCQ2), IC22.N4 (VCCQ3), IC22.P3 (VCCQ4), IC22.P5 (VCCQ5), OSC1.4 (VCC), P2.5 (TVDD), P9.3, P9.4, R1.2, R2.2, R3.2, R4.2, R5.2, R6.2, R7.2, R12.2, R13.2, R16.2, R18.2, R20.2, R21.1, R23.2, R25.2, R28.2, R30.2, R31.2, R32.1, R33.2, R40.1, R41.1, R42.1, R43.1, R48.1, R50.1, R53.1, R58.2, R76.2, R78.2, R80.2, R82.2, R89.1, R120.1, R121.1, R122.1, T2.E, X2.4 (VDD)
VDD_5V: D3.A, IC1.Y5 (VIN_5V_0), IC1.Y6 (VIN_5V_1), P9.5, P9.6, X12.IN
VDD_ADC: IC1.A4 (VDD_ADC_1), IC1.A5 (VDD_ADC_0), IC1.B9 (VREFP_ADC), IC1.D8 (VDDA_ADC), P9.32
VDD_CORE: IC1.F6 (VDD_CORE1)
VDD_MPU: IC1.F10 (VDD_MPU0)
VDD_RTC: IC1.N6 (VDD_RTC4)
VIN_BAT: IC1.Y2 (BAT_1), IC1.Y3 (BAT_2), TP2.P$1
WL_EN: IC11.3 (A2), MOD1.40 (WLAN_EN), R10.1, T3.G
WL_EN.SIP: IC1.K18 (MII1_TXCLK), R136.1
WL_IRQ: IC11.9 (A8), R60.2
WL_IRQ.SIP: IC1.H18 (MII1_REFCLK), R134.1
WL_SDIO_CLK: IC10.6 (A5), R64.2, R103.2
WL_SDIO_CLK.SIP: IC1.L15 (MII1_RXD1), R126.1
WL_SDIO_CMD: IC10.7 (A6), R62.2, R105.2
WL_SDIO_CMD.SIP: IC1.J16 (MII1_TXEN), R86.1
WL_SDIO_D0: IC10.1 (A1), R66.2, R98.2
WL_SDIO_D0.SIP: IC1.J17 (MII1_RXDV), R130.1
WL_SDIO_D1: IC10.3 (A2), R68.2, R99.2
WL_SDIO_D1.SIP: IC1.J18 (MII1_TXD3), R129.1
WL_SDIO_D2: IC10.4 (A3), R70.2, R101.2
WL_SDIO_D2.SIP: IC1.K15 (MII1_TXD2), R128.1
WL_SDIO_D3: IC10.5 (A4), R72.2, R102.2
WL_SDIO_D3.SIP: IC1.H16 (MII1_COL), R127.1
XDMA_EVENT_INTRO: FB5.2, IC13.1 (CLK), P2.17 (EMU2)

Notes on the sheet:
<-- SYS_BOOT0 <-- SYS_BOOT1 <-- SYS_BOOT2 <-- SYS_BOOT3 <-- SYS_BOOT4 <-- SYS_BOOT5 <-- SYS_BOOT6 <-- SYS_BOOT7 <-- SYS_BOOT8 <-- SYS_BOOT9 <-- SYS_BOOT10 <-- SYS_BOOT11 <-- SYS_BOOT12 <-- SYS_BOOT13 <-- SYS_BOOT14 <-- SYS_BOOT15
uSD BOOT
Power
RESET#
USB Device
USB Host
EEPROM
HDMI Interface
BeagleBone Black Configuration
BeagleBone Black Headers
USER LEDs
eMMC 4GB
JTAG
Did not include the transistor array
Used a tantalum cap instead of the large aluminum cap
We are using fuse instead of the PCE power Trip
uSD Connector
SEE NOTES IN GREEN
WiFi Module
1.8V WiFi Power Regulator
OSD3358 SiP
Prototyped by: GHI Electronics, LLC
GHI-PROTO-BBBW-REV-A5
